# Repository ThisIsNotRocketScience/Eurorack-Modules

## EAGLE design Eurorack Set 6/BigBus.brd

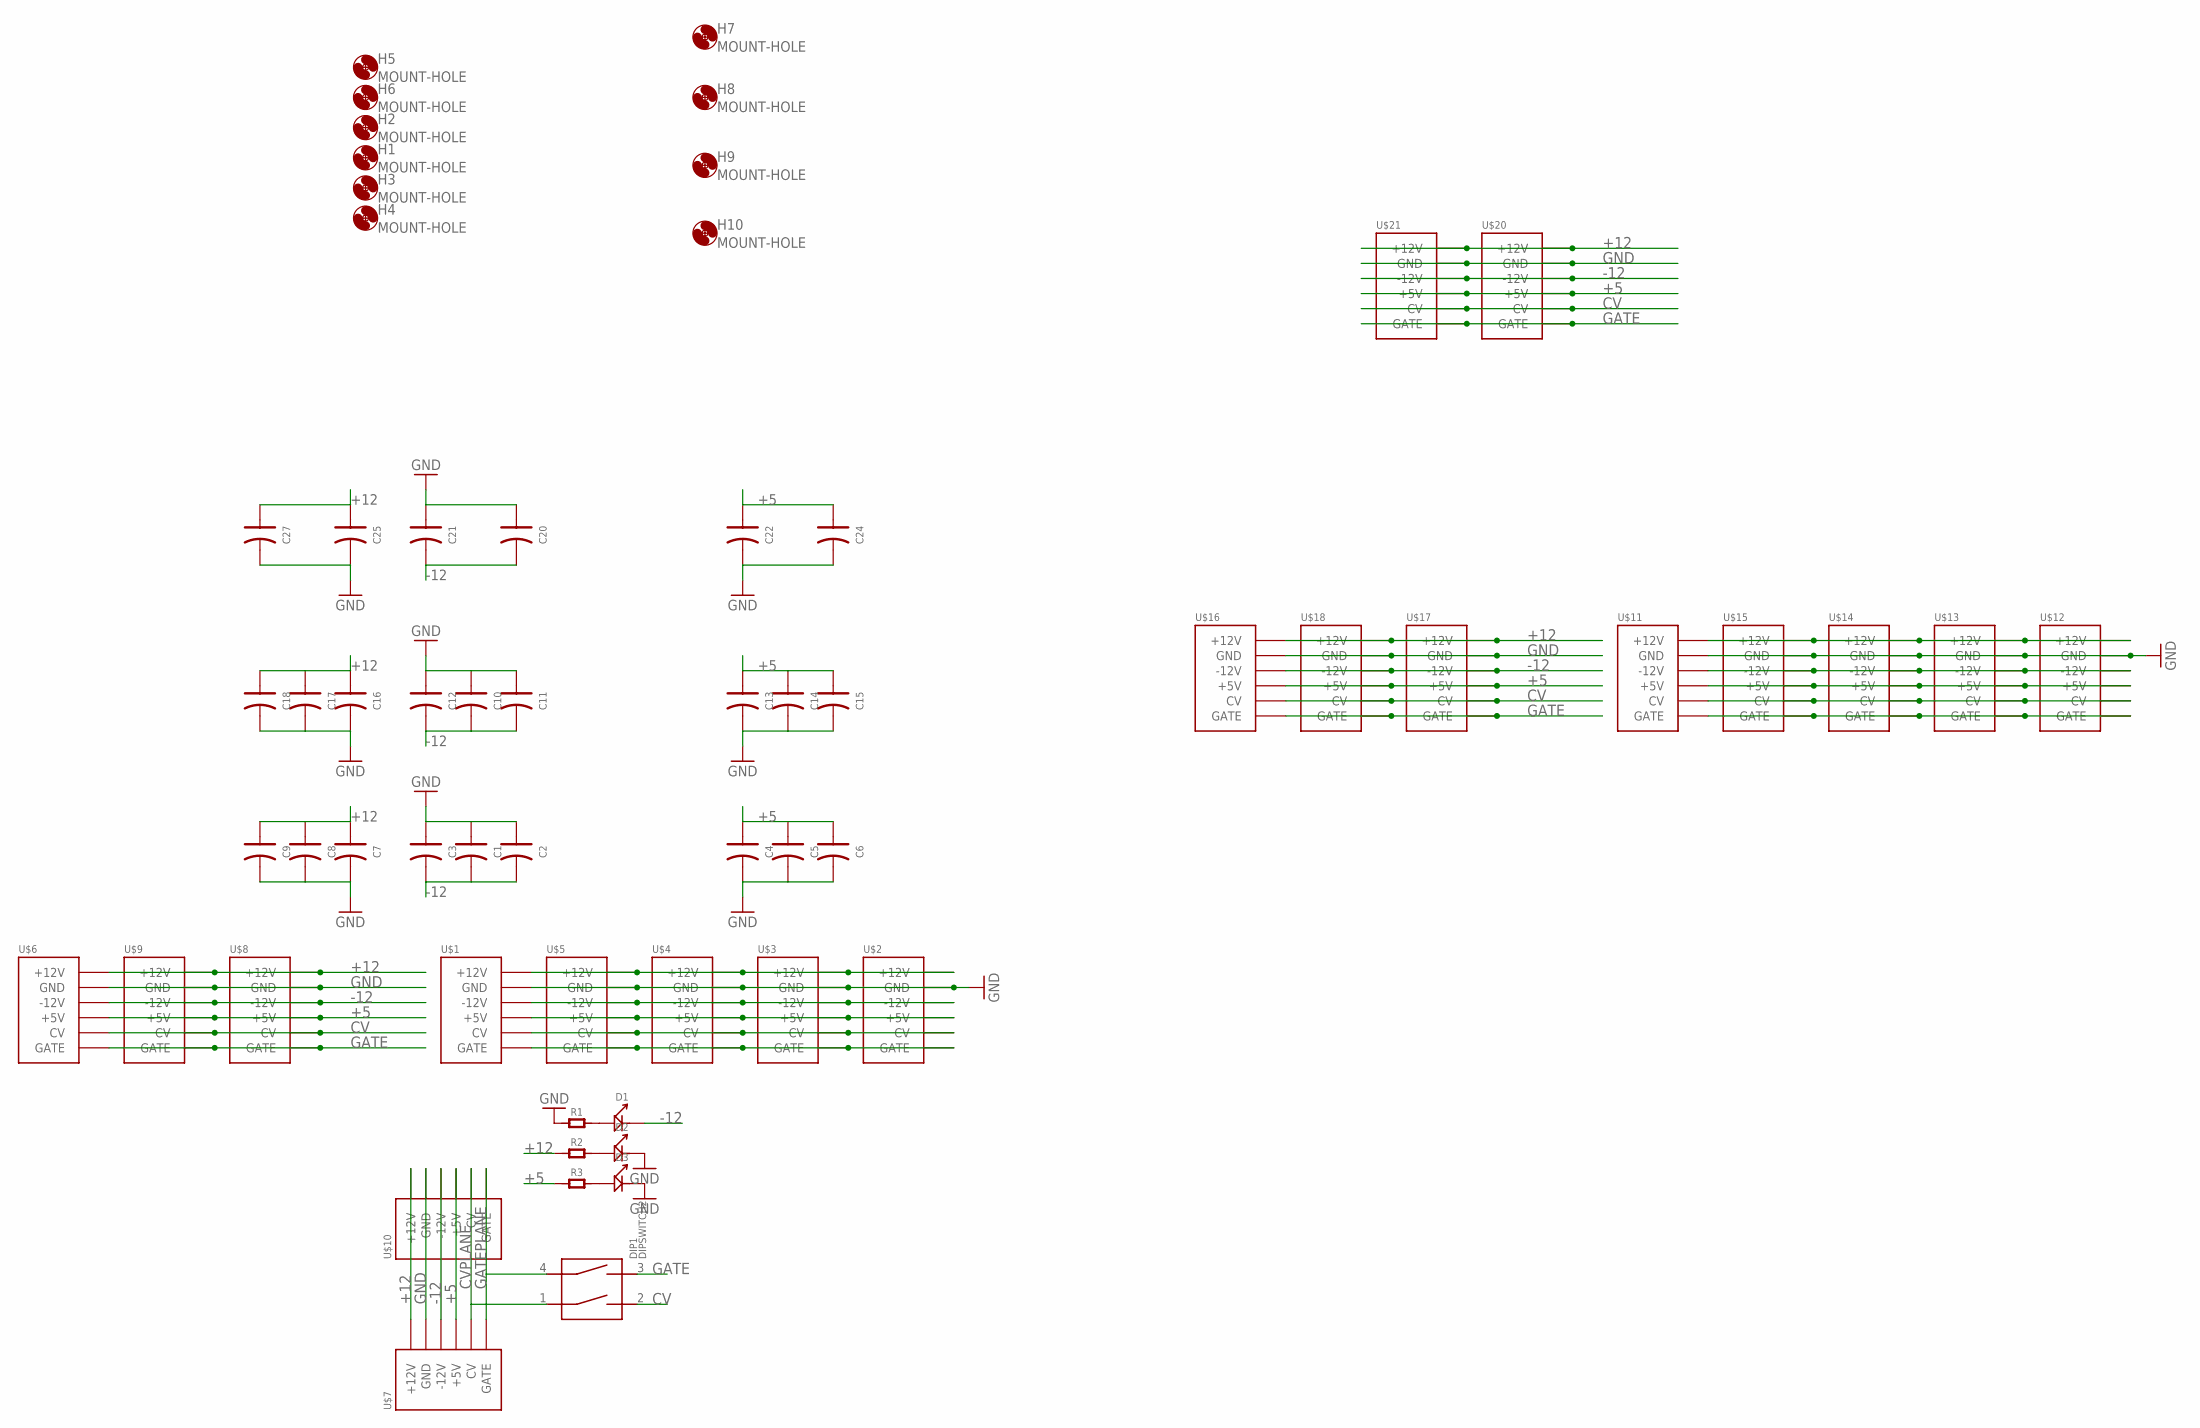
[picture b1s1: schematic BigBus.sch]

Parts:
C1, C2, C3, C4, C5, C6, C7, C8, C9, C10, C11, C12, C13, C14, C15, C16, C17, C18, C20, C21, C22, C24, C25, C27: C-POLAR-A; AVX-A
D1, D2, D3: LED; LED0603
DIP1: DIPSWITCH2
H1, H2, H3, H4, H5, H6, H7, H8, H9, H10: MOUNT-HOLE; 3.2-NOMARKINGS-SMALLSAFEZONE
R1, R2, R3: R-0603; R0603
U$1, U$2, U$3, U$4, U$5, U$6, U$7, U$8, U$9, U$10, U$11, U$12, U$13, U$14, U$15, U$16, U$17, U$18, U$20, U$21: POWER; POWER_16

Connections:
+5: C4.+ (1), C5.+ (1), C6.+ (1), C13.+ (1), C14.+ (1), C15.+ (1), C22.+ (1), C24.+ (1), R3.1, U$1.11 (+5V), U$1.12 (+5V), U$2.11 (+5V), U$2.12 (+5V), U$3.11 (+5V), U$3.12 (+5V), U$4.11 (+5V), U$4.12 (+5V), U$5.11 (+5V), U$5.12 (+5V), U$6.11 (+5V), U$6.12 (+5V), U$7.11 (+5V), U$7.12 (+5V), U$8.11 (+5V), U$8.12 (+5V), U$9.11 (+5V), U$9.12 (+5V), U$10.11 (+5V), U$10.12 (+5V), U$11.11 (+5V), U$11.12 (+5V), U$12.11 (+5V), U$12.12 (+5V), U$13.11 (+5V), U$13.12 (+5V), U$14.11 (+5V), U$14.12 (+5V), U$15.11 (+5V), U$15.12 (+5V), U$16.11 (+5V), U$16.12 (+5V), U$17.11 (+5V), U$17.12 (+5V), U$18.11 (+5V), U$18.12 (+5V), U$20.11 (+5V), U$20.12 (+5V), U$21.11 (+5V), U$21.12 (+5V)
+12: C7.+ (1), C8.+ (1), C9.+ (1), C16.+ (1), C17.+ (1), C18.+ (1), C25.+ (1), C27.+ (1), R2.1, U$1.9 (+12V), U$1.10 (+12V), U$2.9 (+12V), U$2.10 (+12V), U$3.9 (+12V), U$3.10 (+12V), U$4.9 (+12V), U$4.10 (+12V), U$5.9 (+12V), U$5.10 (+12V), U$6.9 (+12V), U$6.10 (+12V), U$7.9 (+12V), U$7.10 (+12V), U$8.9 (+12V), U$8.10 (+12V), U$9.9 (+12V), U$9.10 (+12V), U$10.9 (+12V), U$10.10 (+12V), U$11.9 (+12V), U$11.10 (+12V), U$12.9 (+12V), U$12.10 (+12V), U$13.9 (+12V), U$13.10 (+12V), U$14.9 (+12V), U$14.10 (+12V), U$15.9 (+12V), U$15.10 (+12V), U$16.9 (+12V), U$16.10 (+12V), U$17.9 (+12V), U$17.10 (+12V), U$18.9 (+12V), U$18.10 (+12V), U$20.9 (+12V), U$20.10 (+12V), U$21.9 (+12V), U$21.10 (+12V)
-12: C1.- (2), C2.- (2), C3.- (2), C10.- (2), C11.- (2), C12.- (2), C20.- (2), C21.- (2), D1.-, U$1.1 (-12V), U$1.2 (-12V), U$2.1 (-12V), U$2.2 (-12V), U$3.1 (-12V), U$3.2 (-12V), U$4.1 (-12V), U$4.2 (-12V), U$5.1 (-12V), U$5.2 (-12V), U$6.1 (-12V), U$6.2 (-12V), U$7.1 (-12V), U$7.2 (-12V), U$8.1 (-12V), U$8.2 (-12V), U$9.1 (-12V), U$9.2 (-12V), U$10.1 (-12V), U$10.2 (-12V), U$11.1 (-12V), U$11.2 (-12V), U$12.1 (-12V), U$12.2 (-12V), U$13.1 (-12V), U$13.2 (-12V), U$14.1 (-12V), U$14.2 (-12V), U$15.1 (-12V), U$15.2 (-12V), U$16.1 (-12V), U$16.2 (-12V), U$17.1 (-12V), U$17.2 (-12V), U$18.1 (-12V), U$18.2 (-12V), U$20.1 (-12V), U$20.2 (-12V), U$21.1 (-12V), U$21.2 (-12V)
CV: DIP1.2, U$1.13 (CV), U$1.14 (CV), U$2.13 (CV), U$2.14 (CV), U$3.13 (CV), U$3.14 (CV), U$4.13 (CV), U$4.14 (CV), U$5.13 (CV), U$5.14 (CV), U$6.13 (CV), U$6.14 (CV), U$8.13 (CV), U$8.14 (CV), U$9.13 (CV), U$9.14 (CV), U$11.13 (CV), U$11.14 (CV), U$12.13 (CV), U$12.14 (CV), U$13.13 (CV), U$13.14 (CV), U$14.13 (CV), U$14.14 (CV), U$15.13 (CV), U$15.14 (CV), U$16.13 (CV), U$16.14 (CV), U$17.13 (CV), U$17.14 (CV), U$18.13 (CV), U$18.14 (CV), U$20.13 (CV), U$20.14 (CV), U$21.13 (CV), U$21.14 (CV)
CVPLANE: DIP1.1, U$7.13 (CV), U$7.14 (CV), U$10.13 (CV), U$10.14 (CV)
GATE: DIP1.3, U$1.15 (GATE), U$1.16 (GATE), U$2.15 (GATE), U$2.16 (GATE), U$3.15 (GATE), U$3.16 (GATE), U$4.15 (GATE), U$4.16 (GATE), U$5.15 (GATE), U$5.16 (GATE), U$6.15 (GATE), U$6.16 (GATE), U$8.15 (GATE), U$8.16 (GATE), U$9.15 (GATE), U$9.16 (GATE), U$11.15 (GATE), U$11.16 (GATE), U$12.15 (GATE), U$12.16 (GATE), U$13.15 (GATE), U$13.16 (GATE), U$14.15 (GATE), U$14.16 (GATE), U$15.15 (GATE), U$15.16 (GATE), U$16.15 (GATE), U$16.16 (GATE), U$17.15 (GATE), U$17.16 (GATE), U$18.15 (GATE), U$18.16 (GATE), U$20.15 (GATE), U$20.16 (GATE), U$21.15 (GATE), U$21.16 (GATE)
GATEPLANE: DIP1.4, U$7.15 (GATE), U$7.16 (GATE), U$10.15 (GATE), U$10.16 (GATE)
GND: C1.+ (1), C2.+ (1), C3.+ (1), C4.- (2), C5.- (2), C6.- (2), C7.- (2), C8.- (2), C9.- (2), C10.+ (1), C11.+ (1), C12.+ (1), C13.- (2), C14.- (2), C15.- (2), C16.- (2), C17.- (2), C18.- (2), C20.+ (1), C21.+ (1), C22.- (2), C24.- (2), C25.- (2), C27.- (2), D2.-, D3.-, R1.1, U$1.3 (GND), U$1.4 (GND), U$1.5 (GND), U$1.6 (GND), U$1.7 (GND), U$1.8 (GND), U$2.3 (GND), U$2.4 (GND), U$2.5 (GND), U$2.6 (GND), U$2.7 (GND), U$2.8 (GND), U$3.3 (GND), U$3.4 (GND), U$3.5 (GND), U$3.6 (GND), U$3.7 (GND), U$3.8 (GND), U$4.3 (GND), U$4.4 (GND), U$4.5 (GND), U$4.6 (GND), U$4.7 (GND), U$4.8 (GND), U$5.3 (GND), U$5.4 (GND), U$5.5 (GND), U$5.6 (GND), U$5.7 (GND), U$5.8 (GND), U$6.3 (GND), U$6.4 (GND), U$6.5 (GND), U$6.6 (GND), U$6.7 (GND), U$6.8 (GND), U$7.3 (GND), U$7.4 (GND), U$7.5 (GND), U$7.6 (GND), U$7.7 (GND), U$7.8 (GND), U$8.3 (GND), U$8.4 (GND), U$8.5 (GND), U$8.6 (GND), U$8.7 (GND), U$8.8 (GND), U$9.3 (GND), U$9.4 (GND), U$9.5 (GND), U$9.6 (GND), U$9.7 (GND), U$9.8 (GND), U$10.3 (GND), U$10.4 (GND), U$10.5 (GND), U$10.6 (GND), U$10.7 (GND), U$10.8 (GND), U$11.3 (GND), U$11.4 (GND), U$11.5 (GND), U$11.6 (GND), U$11.7 (GND), U$11.8 (GND), U$12.3 (GND), U$12.4 (GND), U$12.5 (GND), U$12.6 (GND), U$12.7 (GND), U$12.8 (GND), U$13.3 (GND), U$13.4 (GND), U$13.5 (GND), U$13.6 (GND), U$13.7 (GND), U$13.8 (GND), U$14.3 (GND), U$14.4 (GND), U$14.5 (GND), U$14.6 (GND), U$14.7 (GND), U$14.8 (GND), U$15.3 (GND), U$15.4 (GND), U$15.5 (GND), U$15.6 (GND), U$15.7 (GND), U$15.8 (GND), U$16.3 (GND), U$16.4 (GND), U$16.5 (GND), U$16.6 (GND), U$16.7 (GND), U$16.8 (GND), U$17.3 (GND), U$17.4 (GND), U$17.5 (GND), U$17.6 (GND), U$17.7 (GND), U$17.8 (GND), U$18.3 (GND), U$18.4 (GND), U$18.5 (GND), U$18.6 (GND), U$18.7 (GND), U$18.8 (GND), U$20.3 (GND), U$20.4 (GND), U$20.5 (GND), U$20.6 (GND), U$20.7 (GND), U$20.8 (GND), U$21.3 (GND), U$21.4 (GND), U$21.5 (GND), U$21.6 (GND), U$21.7 (GND), U$21.8 (GND)
unnamed: D1.+, R1.2
unnamed: D2.+, R2.2
unnamed: D3.+, R3.2

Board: 2 copper layers, 61 parts (0 on the bottom side), 11 nets, no tracks yet.

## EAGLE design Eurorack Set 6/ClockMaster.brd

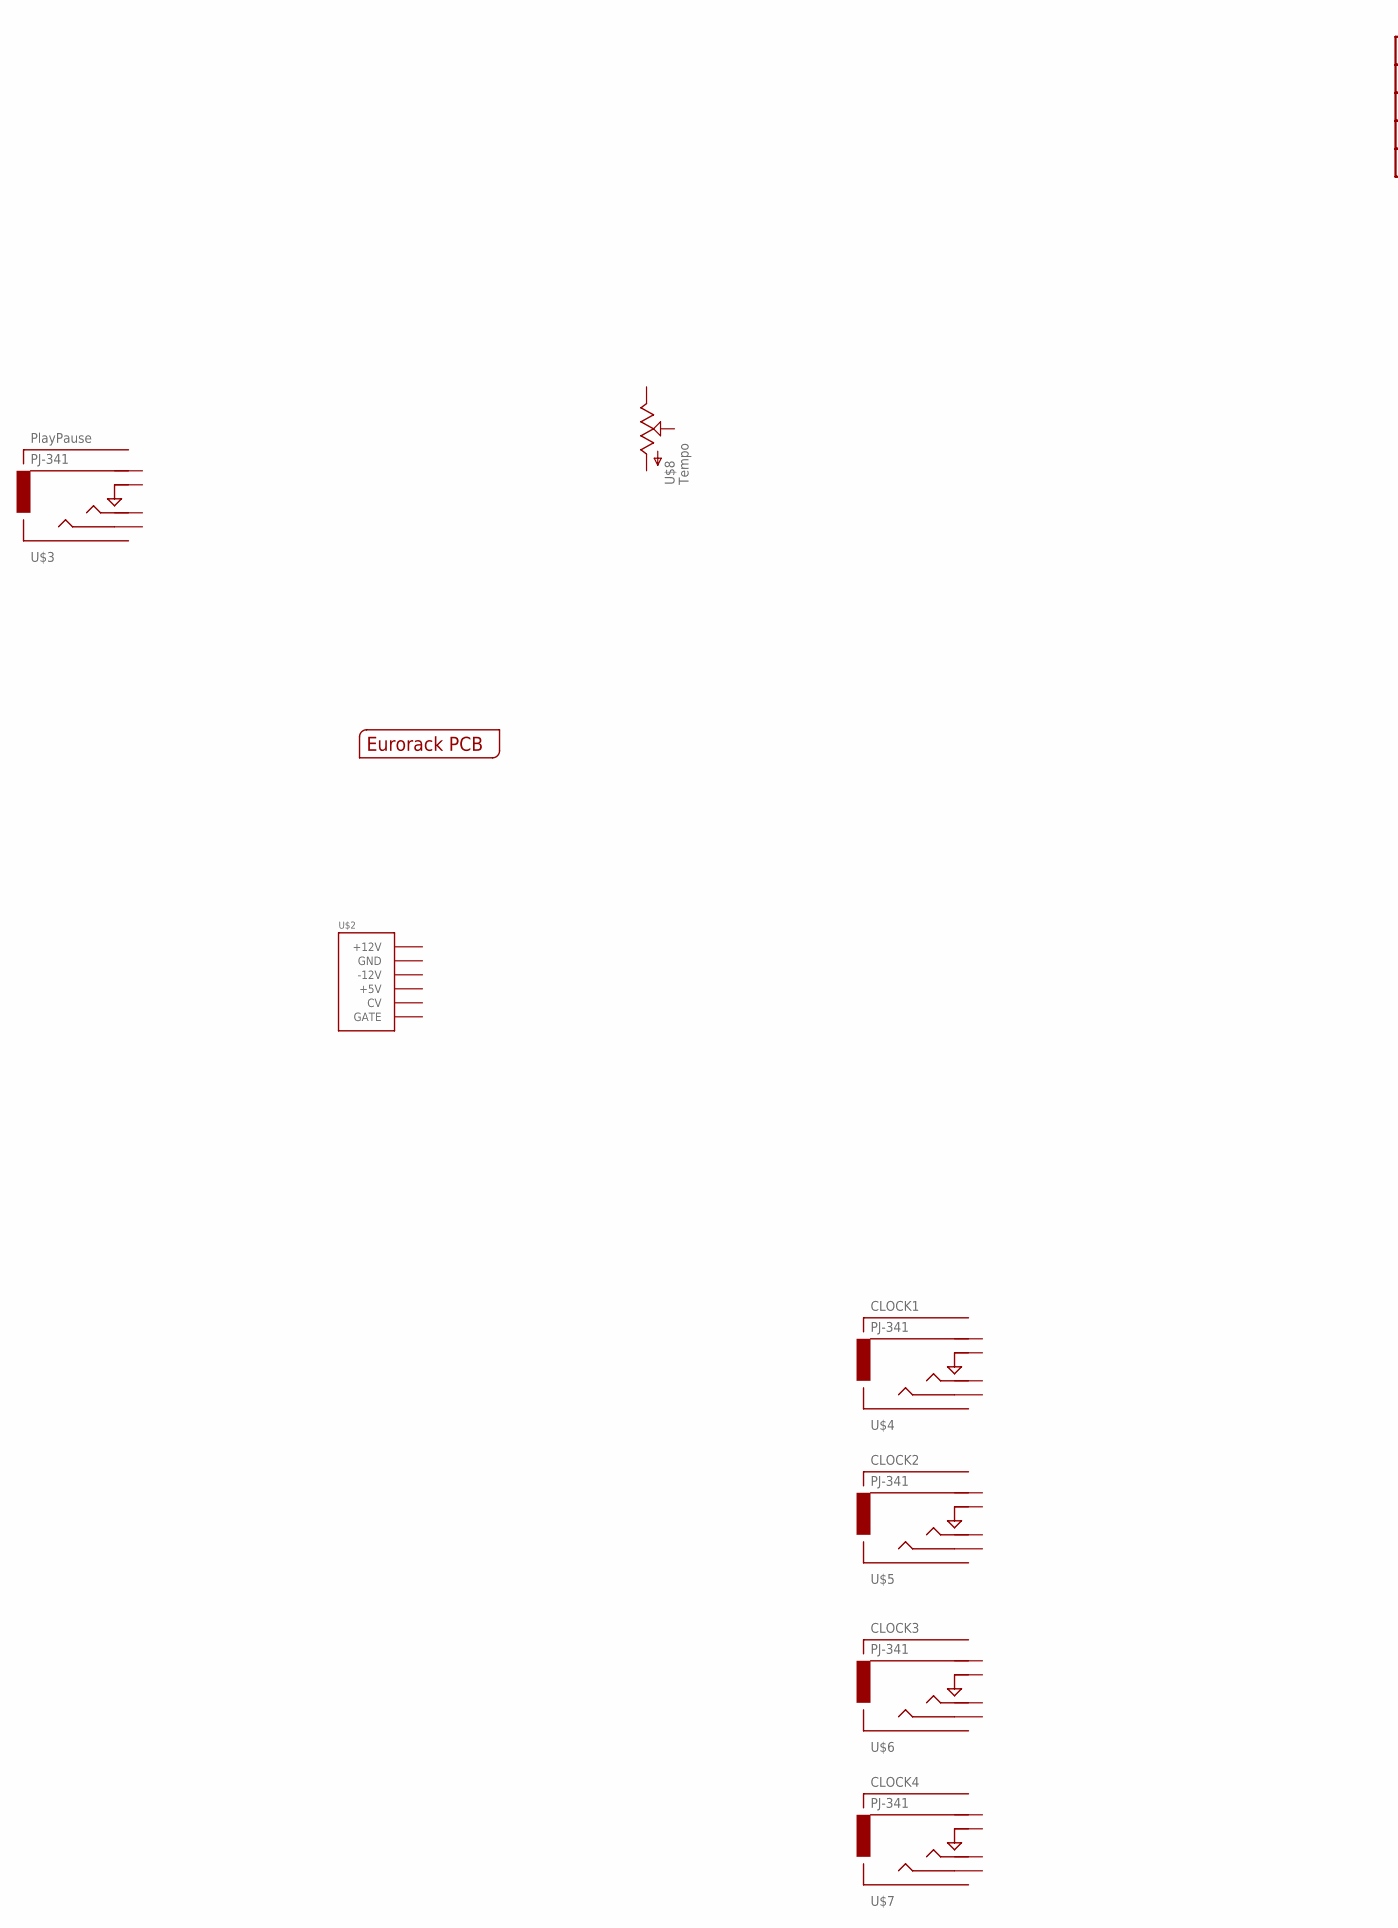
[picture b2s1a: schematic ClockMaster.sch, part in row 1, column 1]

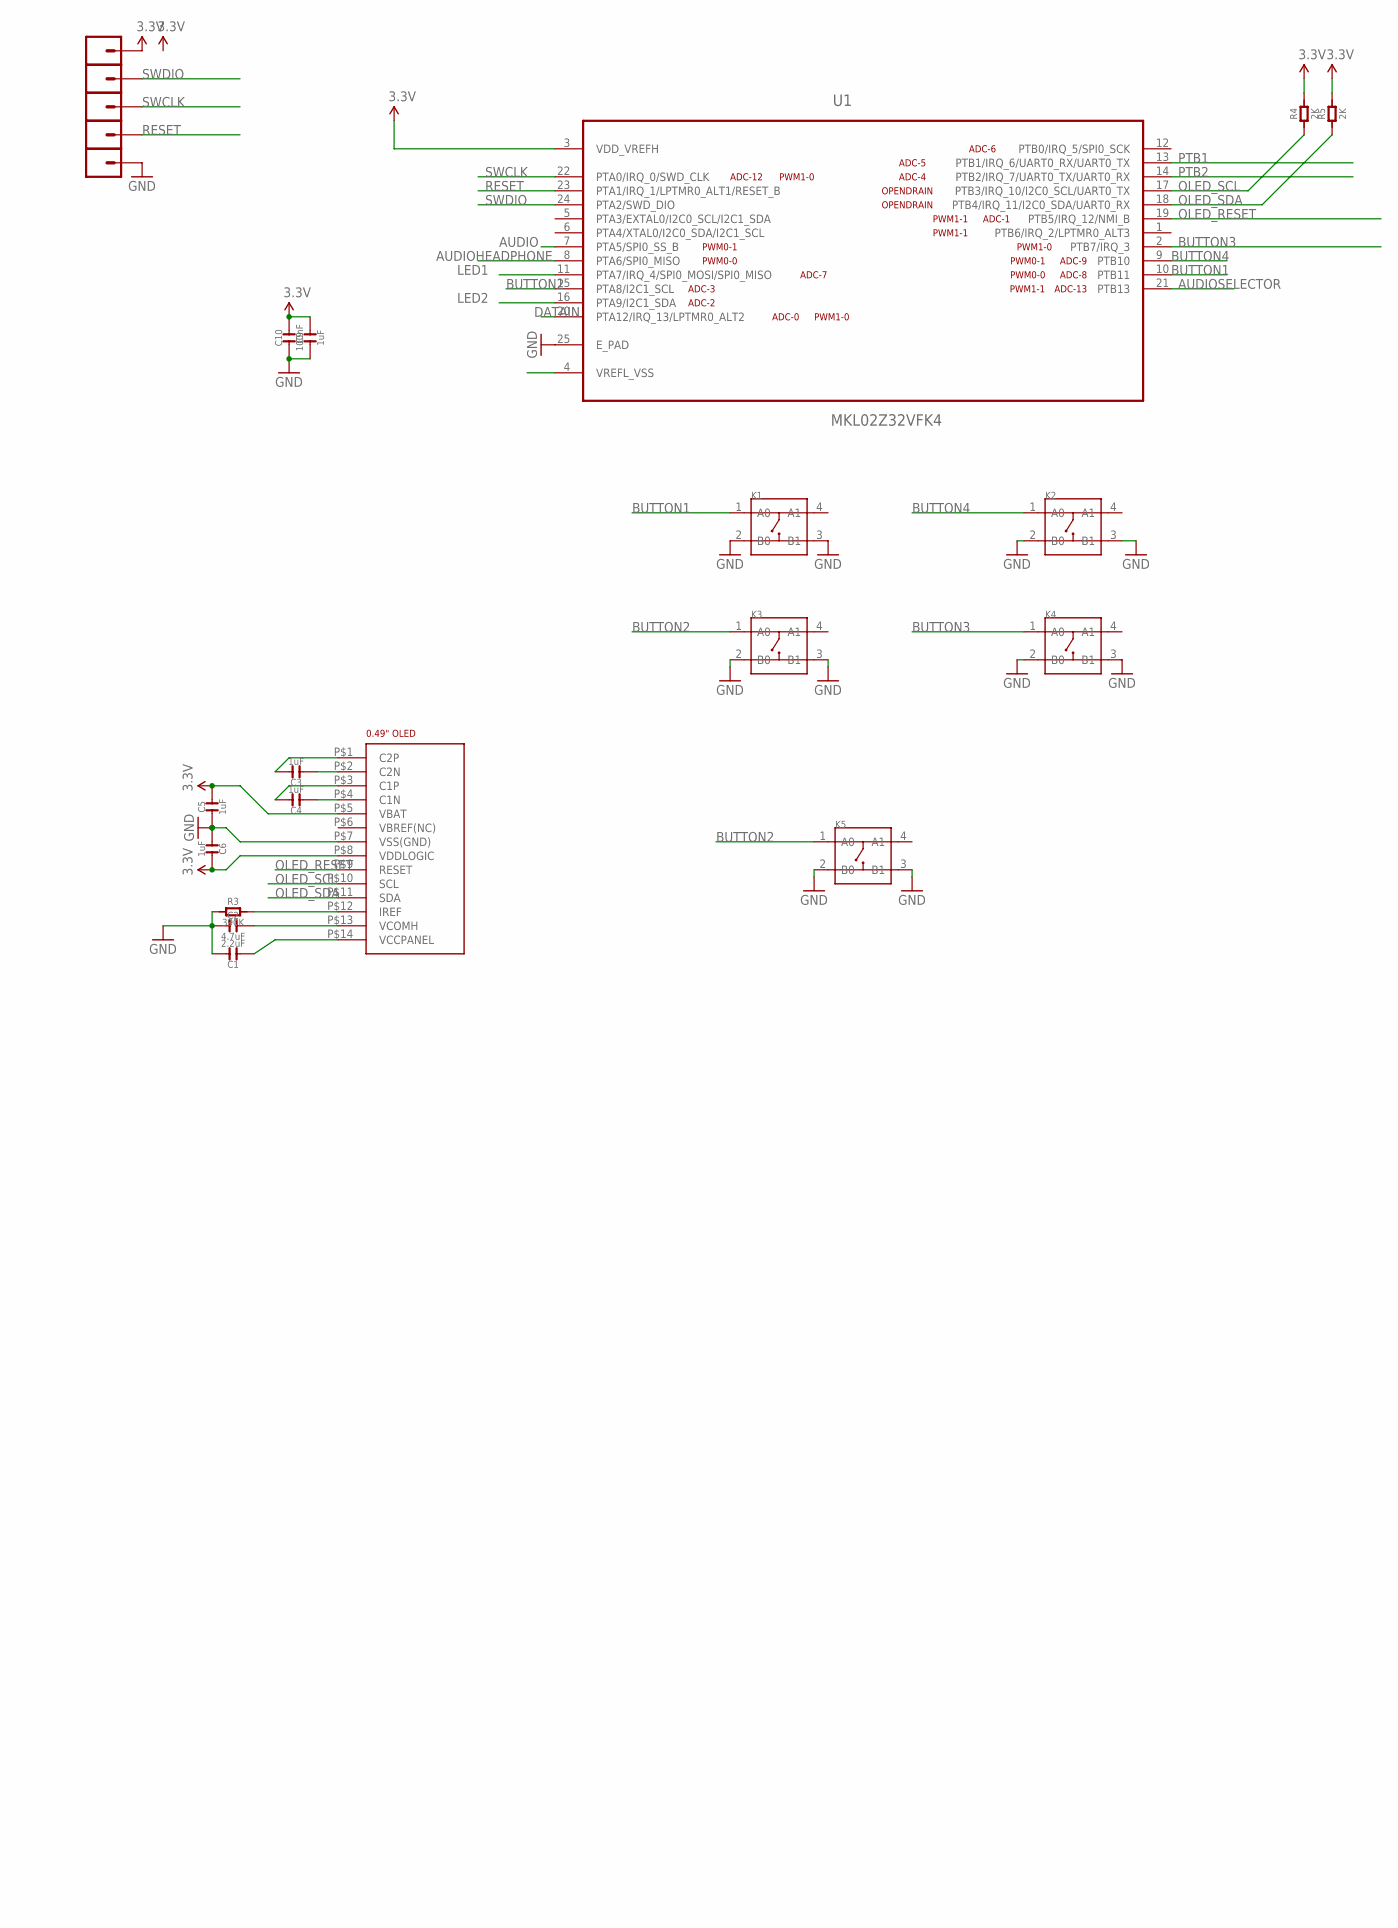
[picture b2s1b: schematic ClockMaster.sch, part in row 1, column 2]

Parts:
C1: 2.2uF; C0603
C2: 4.7uF; C0603
C3, C4, C5, C6, C9: 1uF; C0603
C10: 100nF; C0603
K1, K2, K3, K4, K5: BUTTON-4P-3110040P1; 4P-6.0X6.0X5.0H
PTA6_MISO1, PTA6_MISO2, PTA6_MISO3, PTA6_MISO4, PTA6_MISO5: M01SMD-4.5X1.5; PAD-1.5X4.5
R3: 390K; R0603
R4, R5: 2K; R0603
U1: MKL02Z32VFK4; QFN50P400X400X100-25N
U$1: EURORACK_PCB6HP; EURORACK6HPPCB
U$2: POWER; POWER_16
U$3: PJ-341; 3.5MM-JACK-SWITCH-13MM-INPUT
U$4, U$5, U$6, U$7: PJ-341; 3.5MM-JACK-SWITCH-13MM-OUTPUT
U$8: POTZEPHPOT; OG-POTS_ALPS_POT_VERTICAL
U$9: 0.49"OLEDFOLDED; 0.49"-FPC-0.7-14-FOLDED

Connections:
3.3V: C5.2, C6.2, C9.2, C10.2, PTA6_MISO1.P$1, R4.2, R5.2, U1.3 (VDD_VREFH), U$9.P$5 (VBAT), U$9.P$8 (VDDLOGIC)
AUDIO: U1.7 (PTA5/SPI0_SS_B)
AUDIOHEADPHONE: U1.8 (PTA6/SPI0_MISO)
AUDIOSELECTOR: U1.21 (PTB13)
BUTTON1: K1.1 (A0), U1.10 (PTB11)
BUTTON2: K3.1 (A0), K5.1 (A0), U1.15 (PTA8/I2C1_SCL)
BUTTON3: K4.1 (A0), U1.2 (PTB7/IRQ_3)
BUTTON4: K2.1 (A0), U1.9 (PTB10)
DATAIN: U1.20 (PTA12/IRQ_13/LPTMR0_ALT2)
GND: C1.2, C2.1, C5.1, C6.1, C9.1, C10.1, K1.2 (B0), K1.3 (B1), K2.2 (B0), K2.3 (B1), K3.2 (B0), K3.3 (B1), K4.2 (B0), K4.3 (B1), K5.2 (B0), K5.3 (B1), PTA6_MISO5.P$1, R3.1, U1.25 (E_PAD), U$9.P$7 (VSS(GND))
LED1: U1.11 (PTA7/IRQ_4/SPI0_MOSI/SPI0_MISO)
LED2: U1.16 (PTA9/I2C1_SDA)
unnamed: C3.2, U$9.P$1 (C2P)
unnamed: C4.2, U$9.P$3 (C1P)
unnamed: R3.2, U$9.P$12 (IREF)
unnamed: C1.1, U$9.P$14 (VCCPANEL)
unnamed: C2.2, U$9.P$13 (VCOMH)
unnamed: C3.1, U$9.P$2 (C2N)
unnamed: C4.1, U$9.P$4 (C1N)
OLED_RESET: U1.19 (PTB5/IRQ_12/NMI_B), U$9.P$9 (RESET)
OLED_SCL: R4.1, U1.17 (PTB3/IRQ_10/I2C0_SCL/UART0_TX), U$9.P$10 (SCL)
OLED_SDA: R5.1, U1.18 (PTB4/IRQ_11/I2C0_SDA/UART0_RX), U$9.P$11 (SDA)
PTB1: U1.13 (PTB1/IRQ_6/UART0_RX/UART0_TX)
PTB2: U1.14 (PTB2/IRQ_7/UART0_TX/UART0_RX)
RESET: PTA6_MISO4.P$1, U1.23 (PTA1/IRQ_1/LPTMR0_ALT1/RESET_B)
SWCLK: PTA6_MISO3.P$1, U1.22 (PTA0/IRQ_0/SWD_CLK)
SWDIO: PTA6_MISO2.P$1, U1.24 (PTA2/SWD_DIO)

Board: 2 copper layers, 31 parts (0 on the bottom side), 19 nets, no tracks yet.

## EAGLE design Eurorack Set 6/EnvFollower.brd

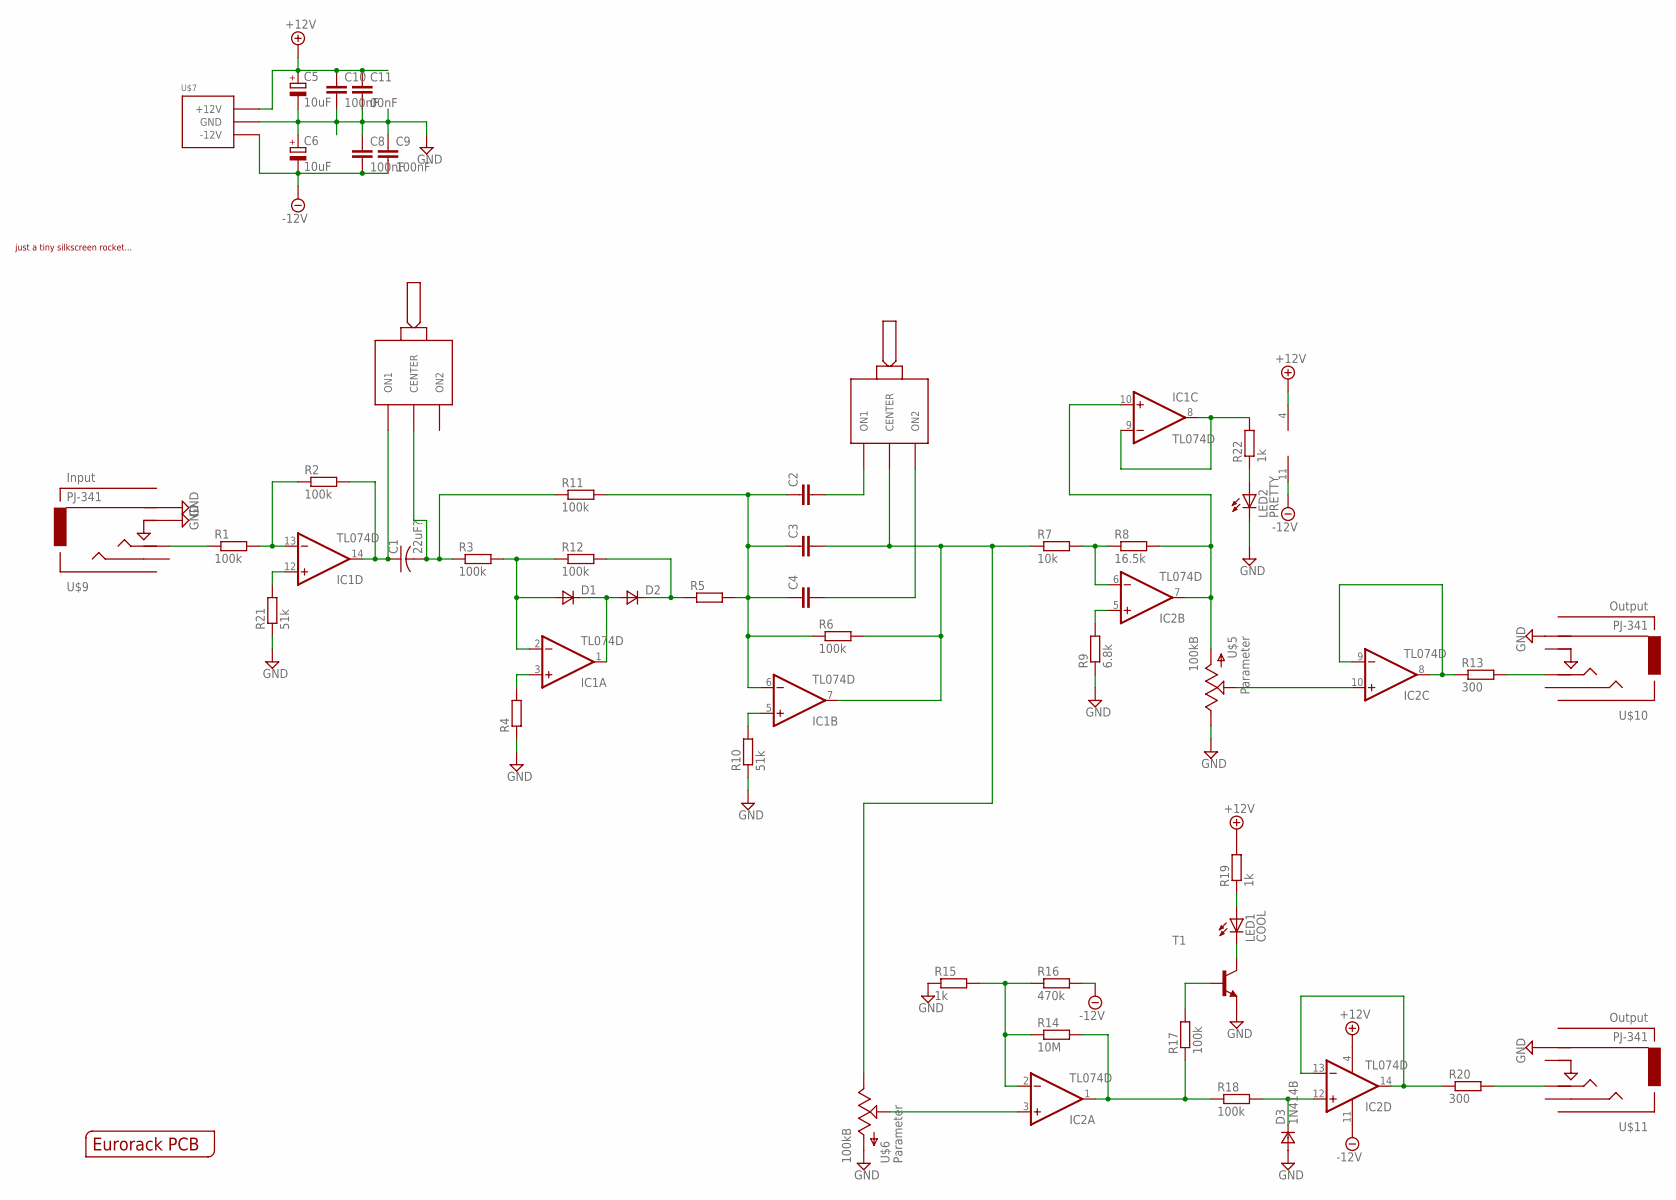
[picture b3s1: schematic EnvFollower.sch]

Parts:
C1: 22uF?; C1210K
C2, C3, C4: C-EUC0603K; C0603K
C5, C6: 10uF; 153CLV-0505
C8, C9, C10: 100nF; C0603K
C11: 00nF; C0603K
D1, D2: DSOT23; SOT-23
D3: 1N414B; SOT-23
IC1, IC2: TL074D; SO14
LED1: COOL; LED3MM
LED2: PRETTY; LED3MM
R1, R2, R3, R6, R11, R12, R17, R18: 100k; R0603
R4, R5: R-EU_R0603; R0603
R7: 10k; R0603
R8: 16.5k; R0603
R9: 6.8k; R0603
R10, R21: 51k; R0603
R13, R20: 300; R0603
R14: 10M; R0603
R15, R19, R22: 1k; R0603
R16: 470k; R0603
T1: BCX70-NPN-SOT23-BEC; SOT23-BEC
U$1: EURORACK_PCB4HP; EURORACK4HPPCB
U$2: JUSTATINYROCKET
U$4, U$8: ONOFFON; MULTICOMP1MS-ONOFFON
U$5, U$6: 100kB; OG-POTS_ALPS_POT_VERTICAL
U$7: POWER_SIMPLE10-OTHERSIDE; POWER_10_LABELSOTHERSIDE
U$9: PJ-341; 3.5MM-JACK-SWITCH-13MM-INPUT
U$10, U$11: PJ-341; 3.5MM-JACK-SWITCH-13MM-OUTPUT

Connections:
+12V: C5.+, C10.1, C11.1, IC1.4 (V+), IC2.4 (V+), R19.2, U$7.9 (+12V), U$7.10 (+12V)
-12V: C6.-, C8.2, C9.2, IC1.11 (V-), IC2.11 (V-), R16.2, U$7.1 (-12V), U$7.2 (-12V)
GND: C5.-, C6.+, C8.1, C9.1, C10.2, C11.2, D3.3 (A), LED2.K (C), R4.1, R9.1, R10.1, R15.1, R21.1, T1.E, U$5.P$1 (E), U$6.P$3 (A), U$7.3 (GND), U$7.4 (GND), U$7.5 (GND), U$7.6 (GND), U$7.7 (GND), U$7.8 (GND), U$9.RING@3 (RING), U$9.SWITCH@3 (SWITCH), U$10.RING@3 (RING), U$11.RING@3 (RING)
unnamed: IC1.8 (OUT), IC1.9 (-IN), R22.2
unnamed: D2.1 (C), R5.1, R12.2
unnamed: C2.1, C3.1, C4.1, IC1.6 (-IN), R5.2, R6.1, R11.2
unnamed: R1.1, U$9.TIP@3 (TIP)
unnamed: IC1.13 (-IN), R1.2, R2.1
unnamed: C1.2, R3.1, R11.1, U$4.2 (CENTER)
unnamed: C1.1, IC1.14 (OUT), R2.2, U$4.1 (ON1)
unnamed: LED2.A, R22.1
unnamed: D1.3 (A), IC1.2 (-IN), R3.2, R12.1
unnamed: D1.1 (C), D2.3 (A), IC1.1 (OUT)
unnamed: IC1.3 (+IN), R4.2
unnamed: IC1.12 (+IN), R21.2
unnamed: C3.2, IC1.7 (OUT), R6.2, R7.1, U$6.P$1 (E), U$8.2 (CENTER)
unnamed: C2.2, U$8.1 (ON1)
unnamed: C4.2, U$8.3 (ON2)
unnamed: IC1.5 (+IN), R10.2
unnamed: IC2.6 (-IN), R7.2, R8.1
unnamed: IC2.5 (+IN), R9.2
unnamed: IC1.10 (+IN), IC2.7 (OUT), R8.2, U$5.P$3 (A)
unnamed: IC2.10 (+IN), U$5.P$2 (S)
unnamed: IC2.8 (OUT), IC2.9 (-IN), R13.1
unnamed: R13.2, U$10.TIP@3 (TIP)
unnamed: IC2.2 (-IN), R14.1, R15.2, R16.1
unnamed: IC2.1 (OUT), R14.2, R17.1, R18.1
unnamed: R17.2, T1.B
unnamed: LED1.K (C), T1.C
unnamed: LED1.A, R19.1
unnamed: D3.1 (C), IC2.12 (+IN), R18.2
unnamed: IC2.13 (-IN), IC2.14 (OUT), R20.1
unnamed: R20.2, U$11.TIP@3 (TIP)
unnamed: IC2.3 (+IN), U$6.P$2 (S)

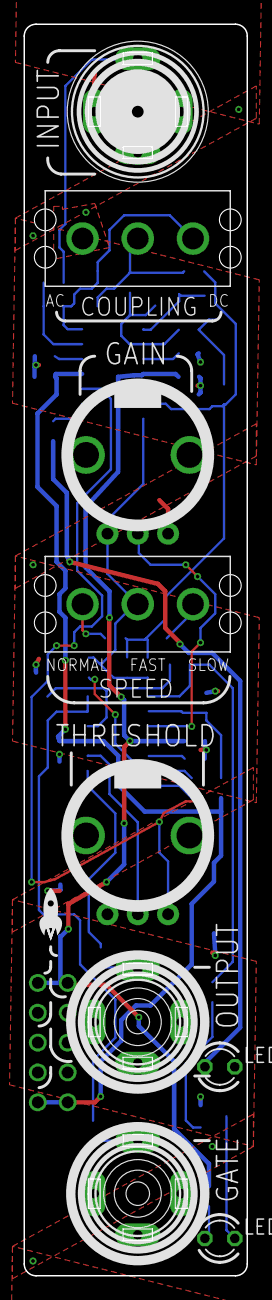
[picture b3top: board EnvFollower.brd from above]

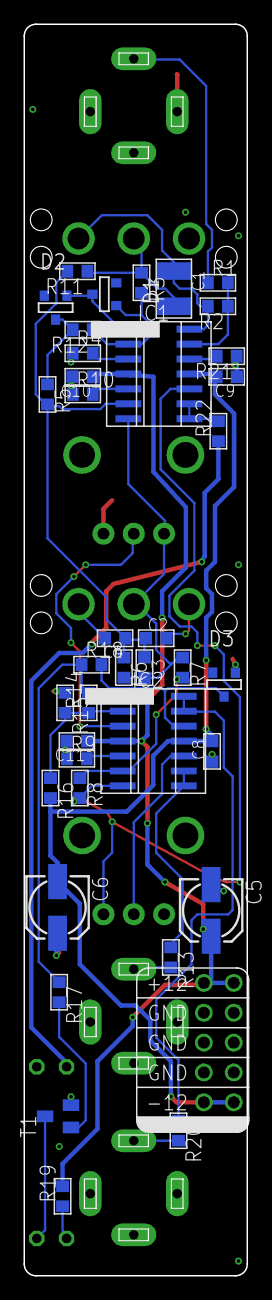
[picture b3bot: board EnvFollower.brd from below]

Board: 2 copper layers, 19.0 x 106.5 mm, 50 parts (39 on the bottom side), 34 nets.

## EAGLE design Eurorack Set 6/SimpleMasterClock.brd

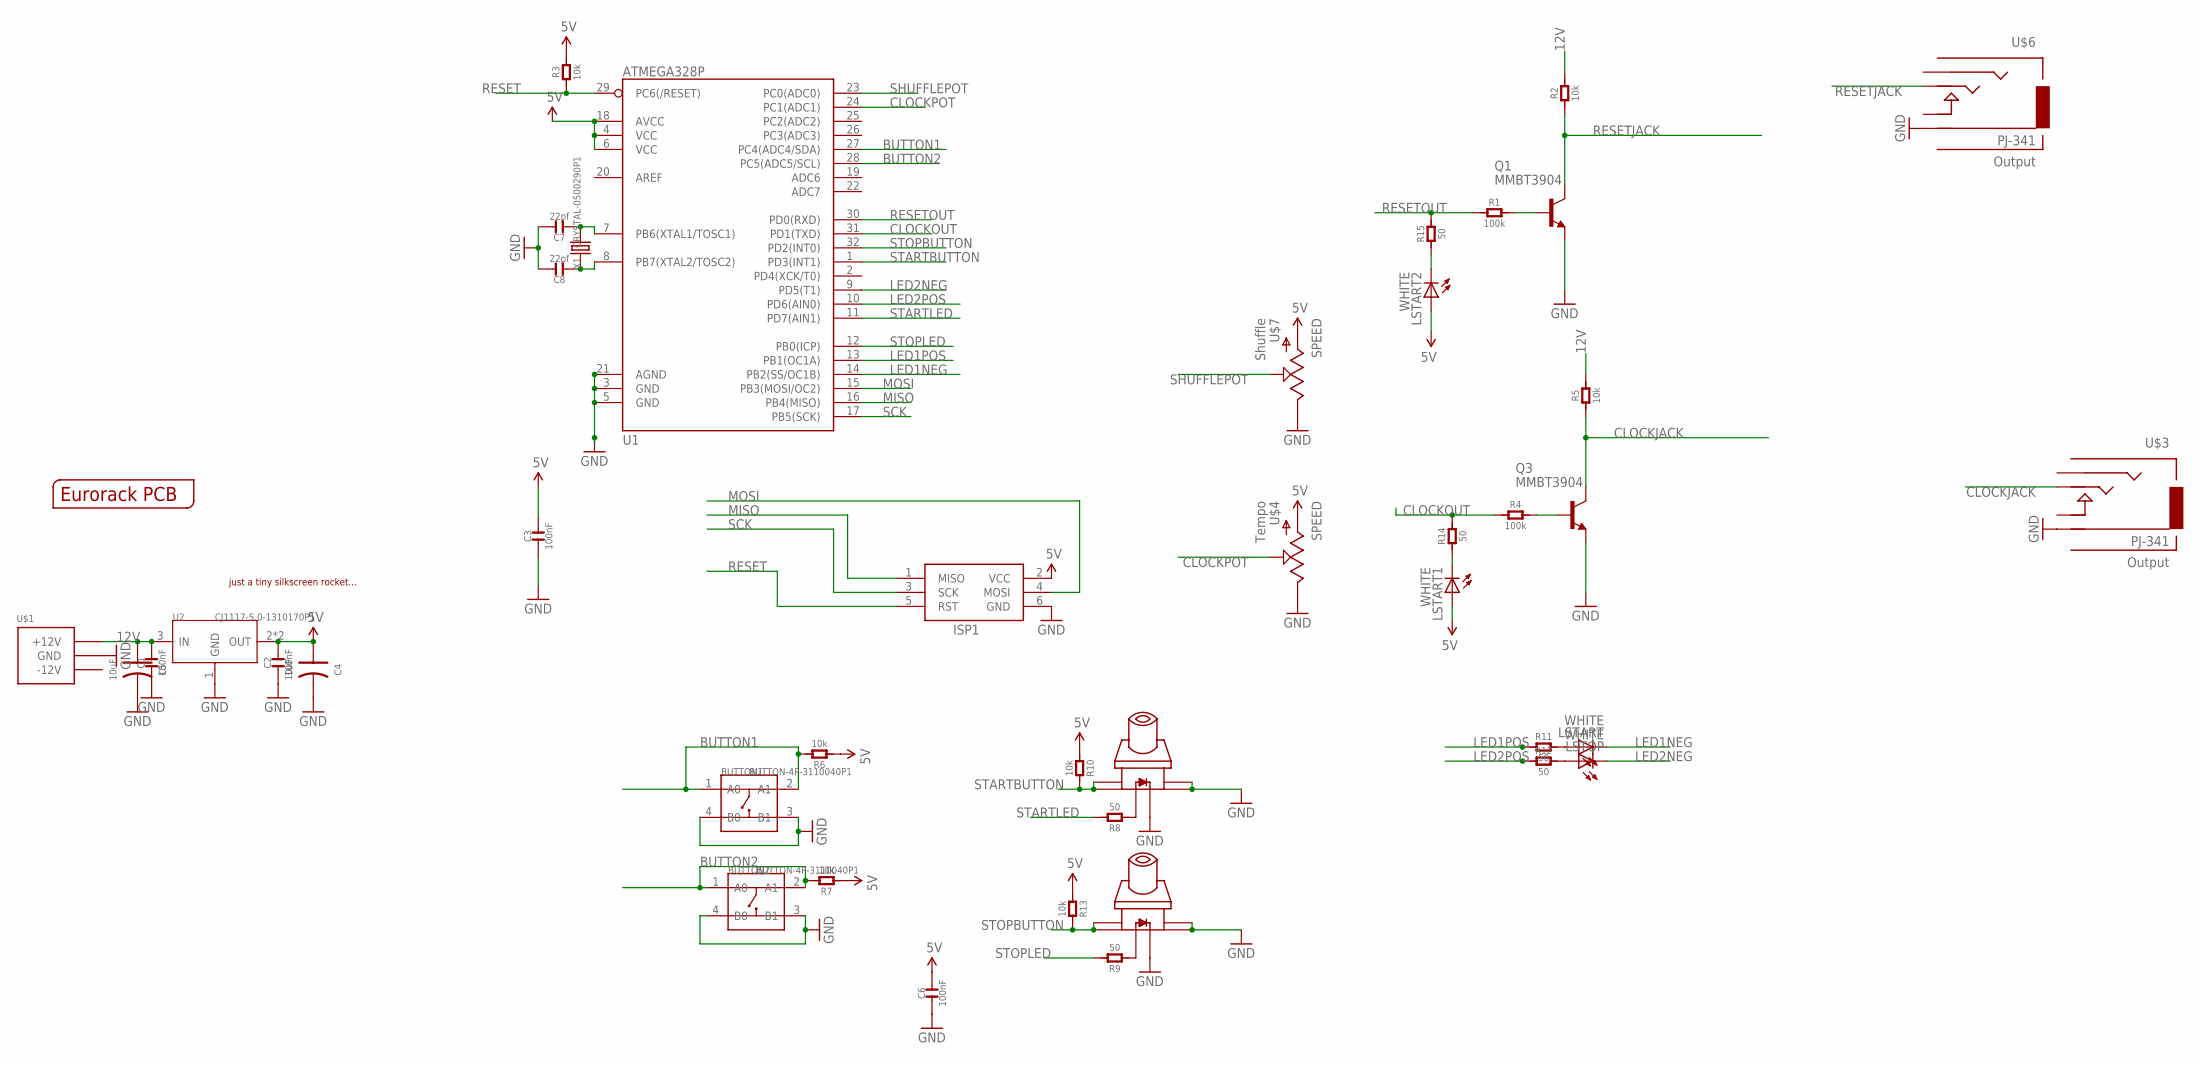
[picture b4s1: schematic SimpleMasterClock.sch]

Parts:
BUTTON1, BUTTON2: BUTTON-4P-3110040P1; 4P-6.0X6.0X5.0H
C1, C2, C3, C6: 100nF; C0603
C4, C5: 10uF; AVX-A
C7, C8: 22pf; C0603
ISP1: AVRISP-6; AVRISP
LSTART, LSTART1, LSTART2: WHITE; LED3MM
LSTOP: WHITE; LED3MM
Q1, Q3: MMBT3904; SOT23-BEC
R1, R4: 100k; R0603
R2, R3, R5, R6, R7, R10, R13: 10k; R0603
R8, R9, R11, R12, R14, R15: 50; R0603
START: SWITCH_W_LED_PB6149L-X-102WHITE; PB6149L
STOP: SWITCH_W_LED_PB6149L-X-102WHITE; PB6149L
U1: ATMEGA328P; TQFP32-08
U2: CJ1117-5.0-1310170P1; SOT223
U$1: POWER_SIMPLE10-OTHERSIDE; POWER_10_LABELSOTHERSIDE
U$2: EURORACK_PCB4HP; EURORACK4HPPCB
U$3, U$6: PJ-341; 3.5MM-JACK-SWITCH-13MM-OUTPUT
U$4, U$7: SPEED; OG-POTS_ALPS_POT_VERTICAL
U$5: JUSTATINYROCKET
X1: CRYSTAL-0500290P1; 2P-SMD-5.0X3.2

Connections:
5V: C2.2, C3.2, C4.+ (1), C6.2, ISP1.2 (VCC), LSTART1.A, LSTART2.A, R3.2, R6.1, R7.1, R10.1, R13.1, U1.4 (VCC), U1.6 (VCC), U1.18 (AVCC), U2.2 (OUT), U2.TER (OUT), U$4.P$3 (A), U$7.P$3 (A)
12V: C1.2, C5.+ (1), R2.2, R5.2, U2.3 (IN), U$1.9 (+12V), U$1.10 (+12V)
BUTTON1: BUTTON1.1 (A0), BUTTON1.2 (A1), R6.2, U1.27 (PC4(ADC4/SDA))
BUTTON2: BUTTON2.1 (A0), BUTTON2.2 (A1), R7.2, U1.28 (PC5(ADC5/SCL))
CLOCKJACK: Q3.C, R5.1, U$3.TIP@3 (TIP)
CLOCKOUT: R4.1, R14.2, U1.31 (PD1(TXD))
CLOCKPOT: U1.24 (PC1(ADC1)), U$4.P$2 (S)
GND: BUTTON1.3 (B1), BUTTON1.4 (B0), BUTTON2.3 (B1), BUTTON2.4 (B0), C1.1, C2.1, C3.1, C4.- (2), C5.- (2), C6.1, C7.2, C8.2, ISP1.6 (GND), Q1.E, Q3.E, START.3, START.4, START.LEDNEG (NEG), STOP.3, STOP.4, STOP.LEDNEG (NEG), U1.3 (GND), U1.5 (GND), U1.21 (AGND), U2.1 (GND), U$1.3 (GND), U$1.4 (GND), U$1.5 (GND), U$1.6 (GND), U$1.7 (GND), U$1.8 (GND), U$3.RING@3 (RING), U$4.P$1 (E), U$6.RING@3 (RING), U$7.P$1 (E)
LED1NEG: LSTART.K (C), U1.14 (PB2(SS/OC1B))
LED1POS: R11.1, U1.13 (PB1(OC1A))
LED2NEG: LSTOP.K (C), U1.9 (PD5(T1))
LED2POS: R12.1, U1.10 (PD6(AIN0))
MISO: ISP1.1 (MISO), U1.16 (PB4(MISO))
MOSI: ISP1.4 (MOSI), U1.15 (PB3(MOSI/OC2))
unnamed: LSTART.A, R11.2
unnamed: LSTOP.A, R12.2
unnamed: R8.1, START.LEDPOS (POS)
unnamed: R9.1, STOP.LEDPOS (POS)
unnamed: C7.1, U1.7 (PB6(XTAL1/TOSC1)), X1.2
unnamed: C8.1, U1.8 (PB7(XTAL2/TOSC2)), X1.1
unnamed: LSTART1.K (C), R14.1
unnamed: LSTART2.K (C), R15.1
unnamed: Q3.B, R4.2
unnamed: Q1.B, R1.2
RESET: ISP1.5 (RST), R3.1, U1.29 (PC6(/RESET))
RESETJACK: Q1.C, R2.1, U$6.TIP@3 (TIP)
RESETOUT: R1.1, R15.2, U1.30 (PD0(RXD))
SCK: ISP1.3 (SCK), U1.17 (PB5(SCK))
SHUFFLEPOT: U1.23 (PC0(ADC0)), U$7.P$2 (S)
STARTBUTTON: R10.2, START.1, START.2, U1.1 (PD3(INT1))
STARTLED: R8.2, U1.11 (PD7(AIN1))
STOPBUTTON: R13.2, STOP.1, STOP.2, U1.32 (PD2(INT0))
STOPLED: R9.2, U1.12 (PB0(ICP))

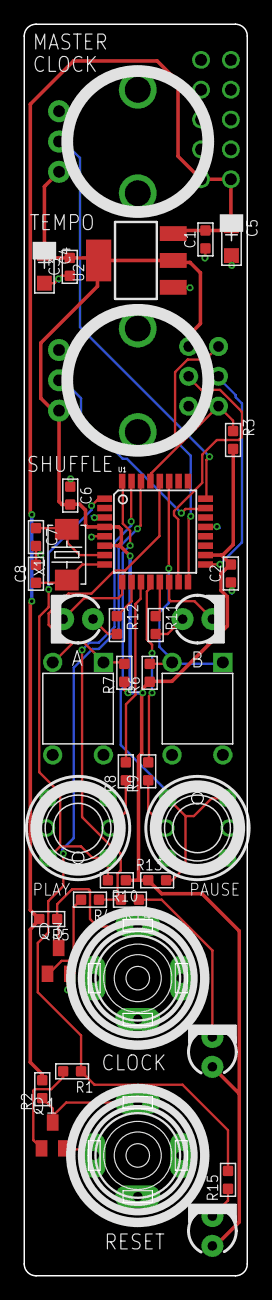
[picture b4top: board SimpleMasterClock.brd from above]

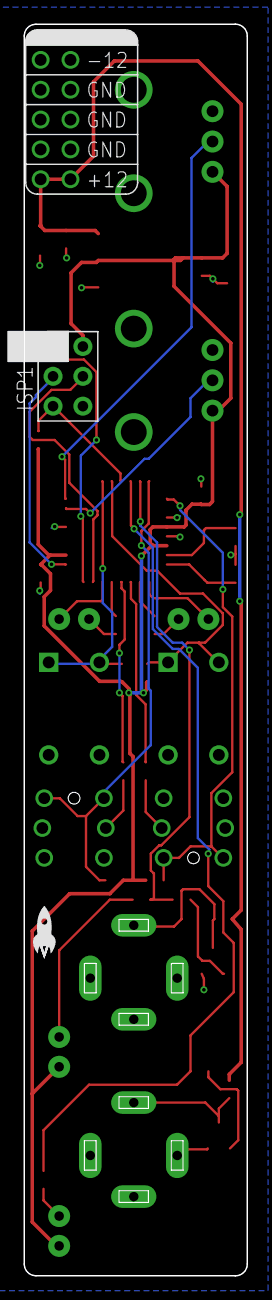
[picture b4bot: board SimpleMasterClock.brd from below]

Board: 2 copper layers, 19.0 x 106.5 mm, 44 parts (3 on the bottom side), 33 nets.

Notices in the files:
parts and their libraries:
SparkFun-Aesthetics: Licensing: CC v3.0 Share-Alike You are welcome to use this library for commercial purposes.
